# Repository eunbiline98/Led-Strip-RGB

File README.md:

# Led-Strip-RGB
Control a LED strip using an Arduino PWM, an N-Channel MOSFET

# Hardware
- Arduino Uno or Nano Or Mega
- Driver PWM 3 Channel
- Led Strip 24VDC
- PSU 24V 150W / 6.25A

# Component Driver Pwm
- Transistor Mosfet IRF 3205
- Optocoupler PC817
- Resistor 100 Ω
- Resistor 330 Ω
- Resistor 2K2
- Terminal Screw 3 Pin
- Heatsink Transistor

# Datasheet 
- https://www.alldatasheet.com/datasheet-pdf/pdf/68133/IRF/IRF3205L.html
- https://www.alldatasheet.com/datasheet-pdf/pdf/43368/SHARP/PC817.html
- https://www.lighting.philips.co.id/api/assets/v1/file/PhilipsLighting/content/b4c24a16e74241ce97e5a92900c3f3d8/PHL_MI_UNILinear_Flex_BGC301-INI.pdf

# Software
- Arduino IDE
- Eagle PCB Designer

# Documentation

- Shematic driver PWM RGB

- Layout driver PWM RGB 
- 

- Running Test
https://www.instagram.com/p/CMMaT6oABkS/

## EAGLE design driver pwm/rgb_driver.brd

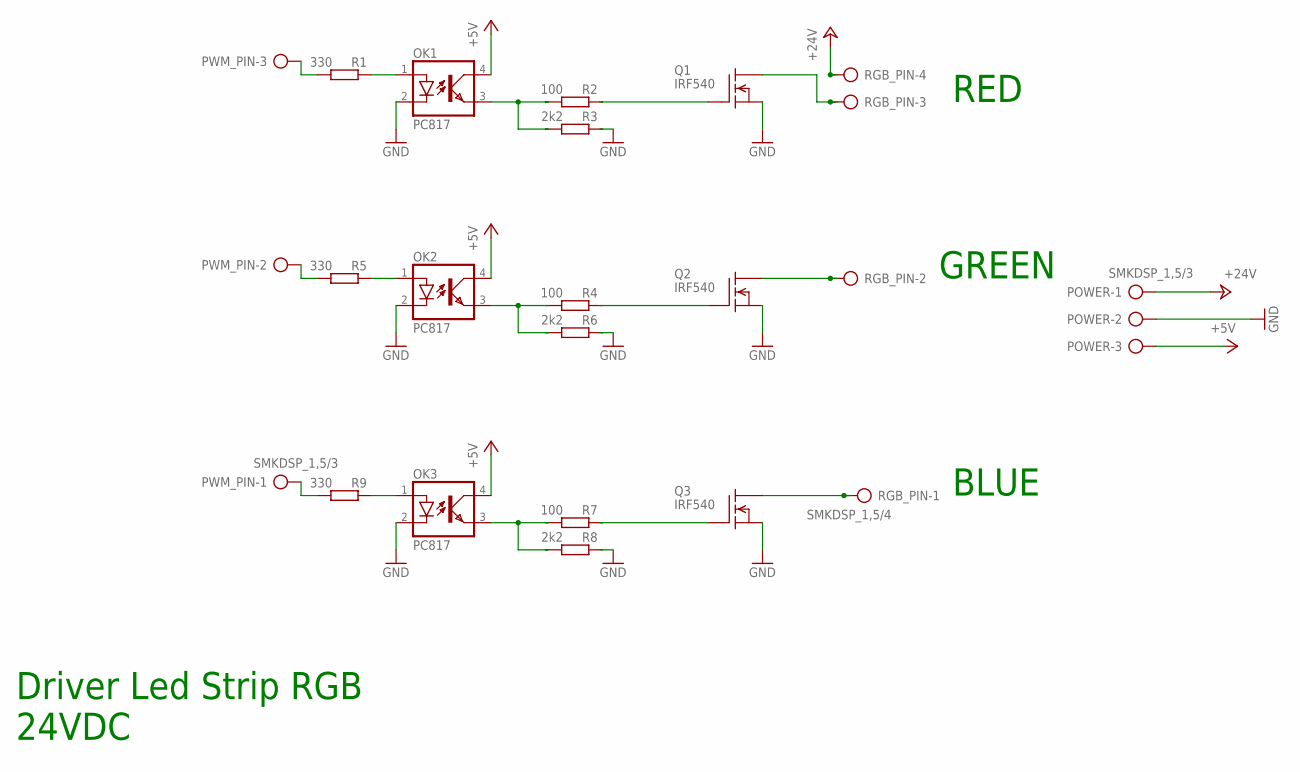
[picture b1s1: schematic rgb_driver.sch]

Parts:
OK1, OK2, OK3: PC817; DIL04
POWER: SMKDSP_1,5/3
PWM_PIN: SMKDSP_1,5/3
Q1, Q2, Q3: IRF540; TO220
R1, R5, R9: 330; 0207/10
R2, R4, R7: 100; 0207/10
R3, R6, R8: 2k2; 0207/10
RGB_PIN: SMKDSP_1,5/4

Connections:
+5V: OK1.4 (COL), OK2.4 (COL), OK3.4 (COL), POWER.3
+24V: POWER.1, RGB_PIN.4
BLUE_LED: Q3.2 (D), RGB_PIN.1
GND: OK1.2 (C), OK2.2 (C), OK3.2 (C), POWER.2, Q1.3 (S), Q2.3 (S), Q3.3 (S), R3.2, R6.2, R8.2
GREEN_LED: Q2.2 (D), RGB_PIN.2
unnamed: OK1.3 (EMIT), R2.1, R3.1
unnamed: Q1.1 (G), R2.2
unnamed: OK2.3 (EMIT), R4.1, R6.1
unnamed: Q2.1 (G), R4.2
unnamed: OK3.3 (EMIT), R7.1, R8.1
unnamed: Q3.1 (G), R7.2
unnamed: OK1.1 (A), R1.2
unnamed: OK2.1 (A), R5.2
unnamed: OK3.1 (A), R9.2
PWM_BLUE: PWM_PIN.1, R9.1
PWM_GREEN: PWM_PIN.2, R5.1
PWM_RED: PWM_PIN.3, R1.1
RED_LED: Q1.2 (D), RGB_PIN.3

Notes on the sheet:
Driver Led Strip RGB
24VDC
RED
GREEN
BLUE

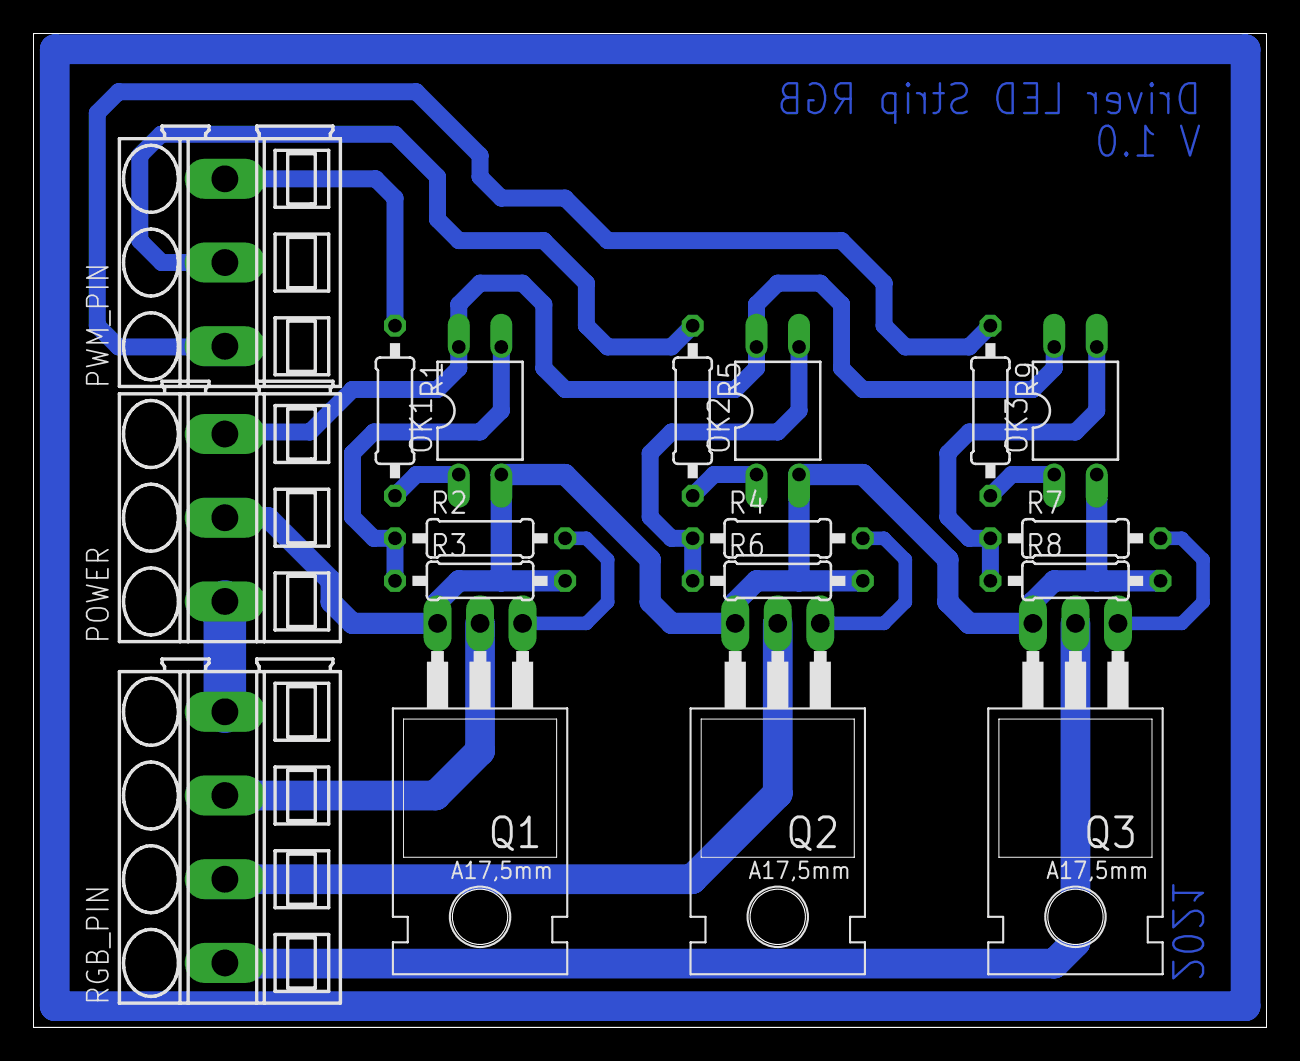
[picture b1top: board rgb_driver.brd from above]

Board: 2 copper layers, 73.6 x 59.4 mm, 18 parts (0 on the bottom side), 18 nets.

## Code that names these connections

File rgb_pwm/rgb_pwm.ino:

#include <PWM.h>

#define RED_LED 3
#define BLUE_LED 5
#define GREEN_LED 5
#define button 8

int btn_mode = 0;
int state = 0;
int btn_status = 0;

int red_state = 0;
int green_state = 0;
int blue_state = 0;
int state_on = 255;

int fadeSpeed = 10;
int32_t frequency = 15000;

void setup() {
  InitTimersSafe();
  SetPinFrequencySafe(RED_LED, frequency);
  SetPinFrequencySafe(GREEN_LED, frequency);
  SetPinFrequencySafe(BLUE_LED, frequency);
}

void led_mode_1() {
  for (int i = 0; i < 256; i++) {
    pwmWrite(RED_LED, red_state);
    red_state += 1;
    delay(fadeSpeed);
  }

  for (int i = 0; i < 256; i++) {
    pwmWrite(BLUE_LED, blue_state);
    blue_state += 1;
    delay(fadeSpeed);
  }

  for (int i = 0; i < 256; i++) {
    pwmWrite(GREEN_LED, green_state);
    green_state += 1;
    delay(fadeSpeed);
  }
}

void led_mode_2() {
  for (int i = 0; i < 256; i++) {
    pwmWrite(GREEN_LED, state_on);
    pwmWrite(RED_LED, state_on);
    pwmWrite(BLUE_LED, state_on);
    state_on -= 1;
    delay(fadeSpeed);
  }
}

void loop() {

  btn_mode = digitalRead(button);
  if (btn_mode == HIGH && state == LOW) {
    Serial.println("Push....");
    btn_status = 1 - btn_status;
  }

  state - btn_mode;

  if (btn_status == HIGH) {
    led_mode_1();
    delay(5000);
    led_mode_2();
  }
  else {
    pwmWrite(RED_LED, 0);
    pwmWrite(GREEN_LED, 0);
    pwmWrite(BLUE_LED, 0);
  }
}

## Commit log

2021-07-19 Adding PCB Design
2021-07-19 Adding sketch arduino
2021-07-25 Add files via upload
    ambience processing
